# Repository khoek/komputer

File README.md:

# komputer

These are files (mainly programs) to help build a computer out of (relatively elementary) ICs.

There is a companion repository [khoek/kcpu-vm](https://github.com/khoek/kcpu-vm) which contains an assembler and hardware-simulating virtual machine for the architecture.

## Contents

- `circuits` - Designs for the various computer modules
- `embedded/tests` - Tests for the various modules
- `tools/eeagle` and `embedded/eeagle` - An EEPROM programmer client--server pair to talk to an Adafruit Metro Mini.

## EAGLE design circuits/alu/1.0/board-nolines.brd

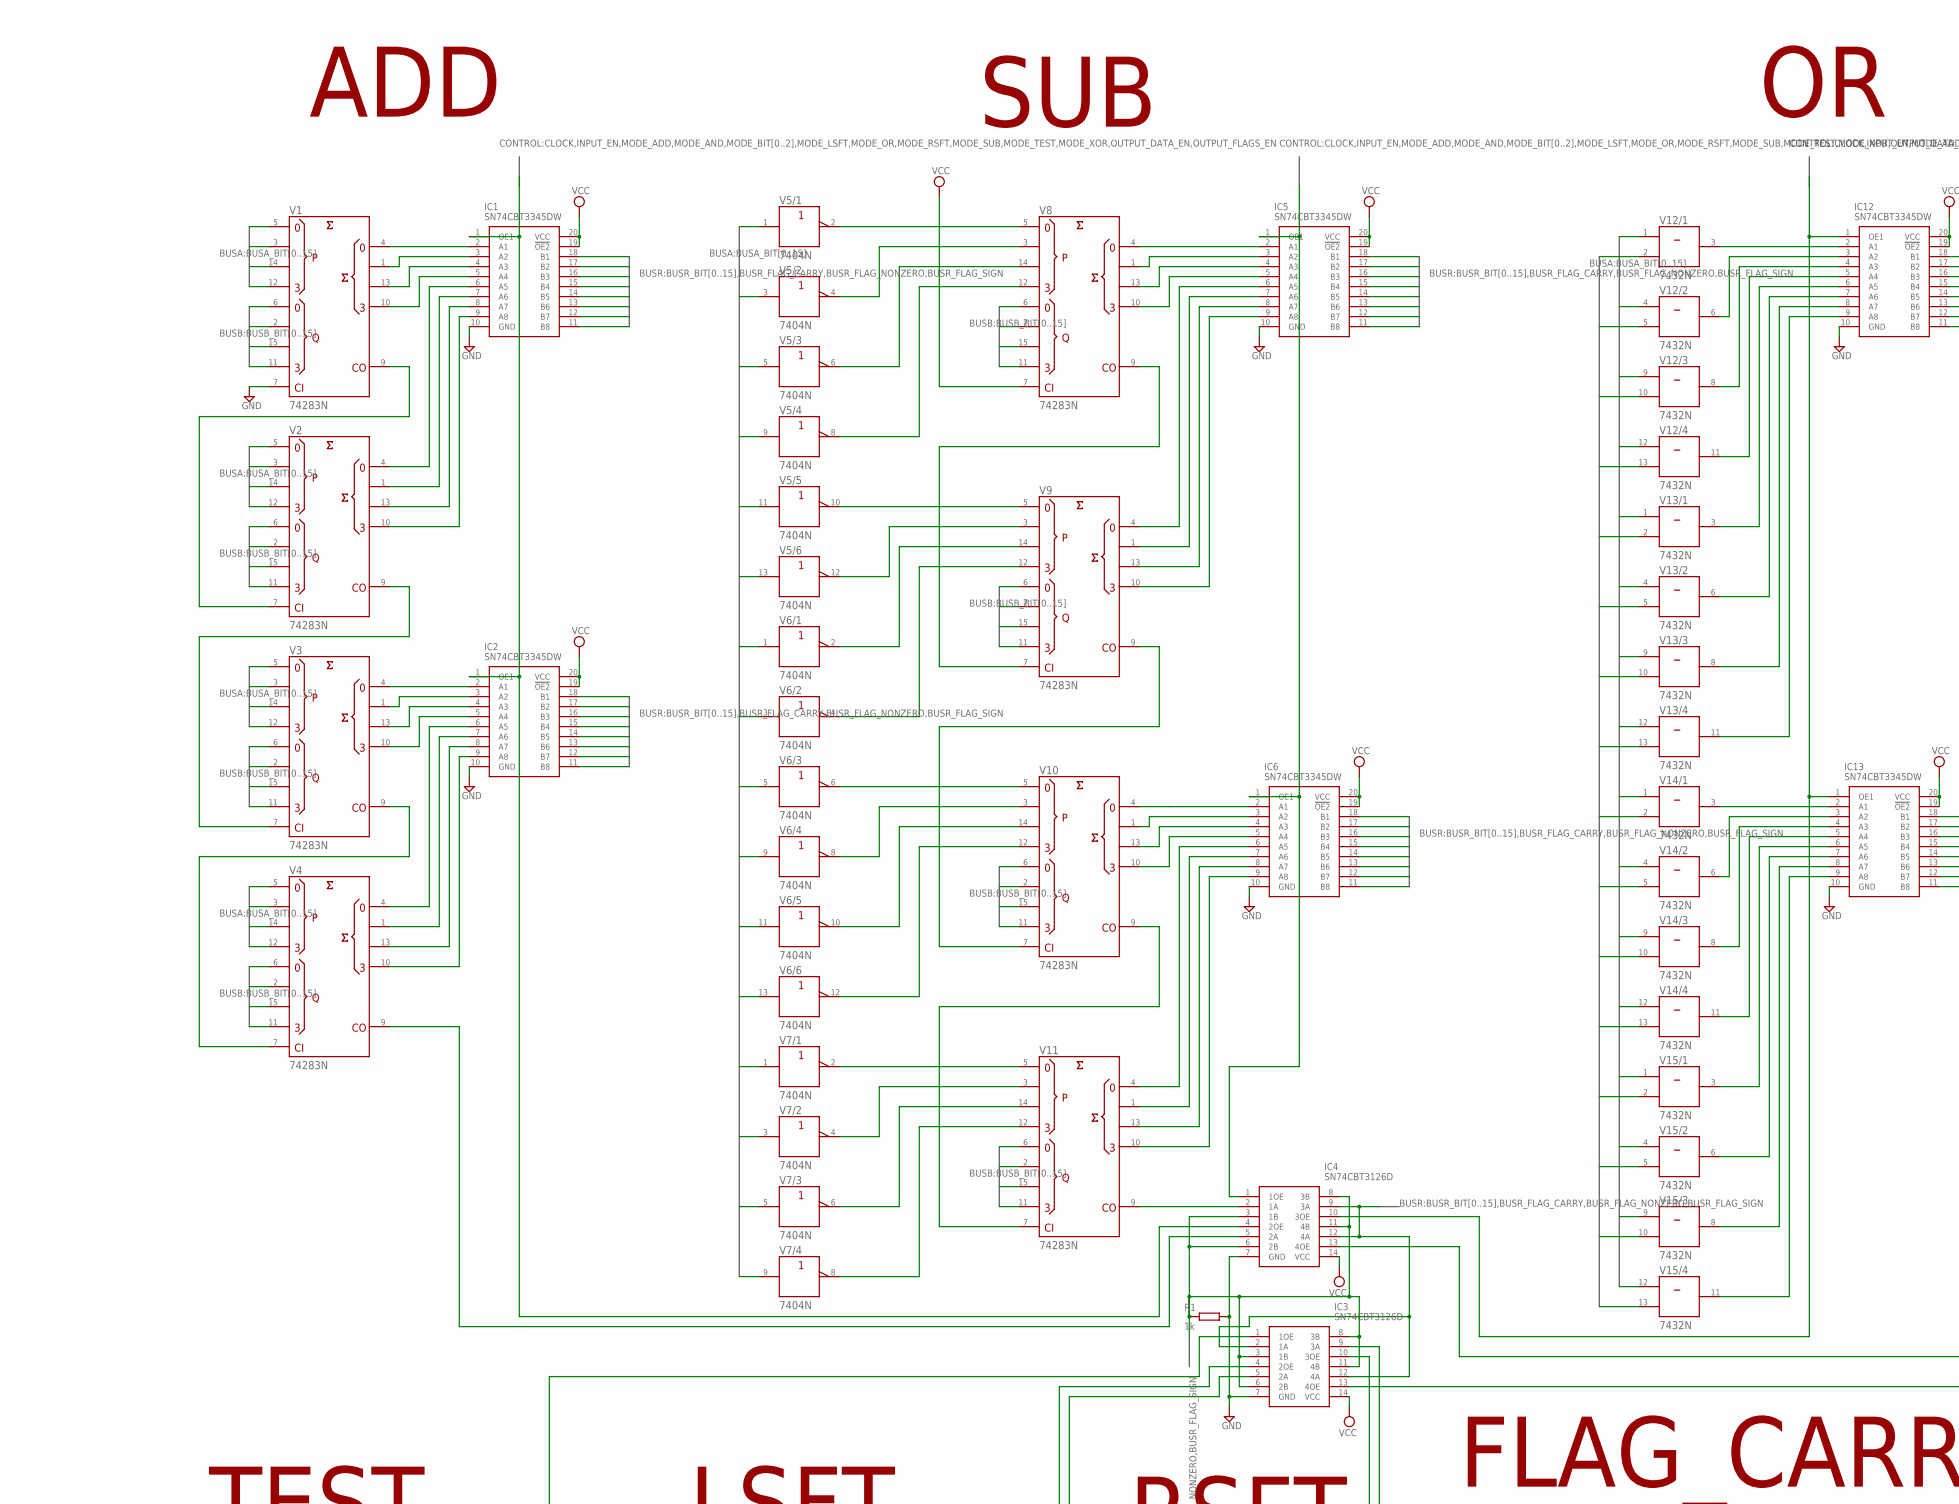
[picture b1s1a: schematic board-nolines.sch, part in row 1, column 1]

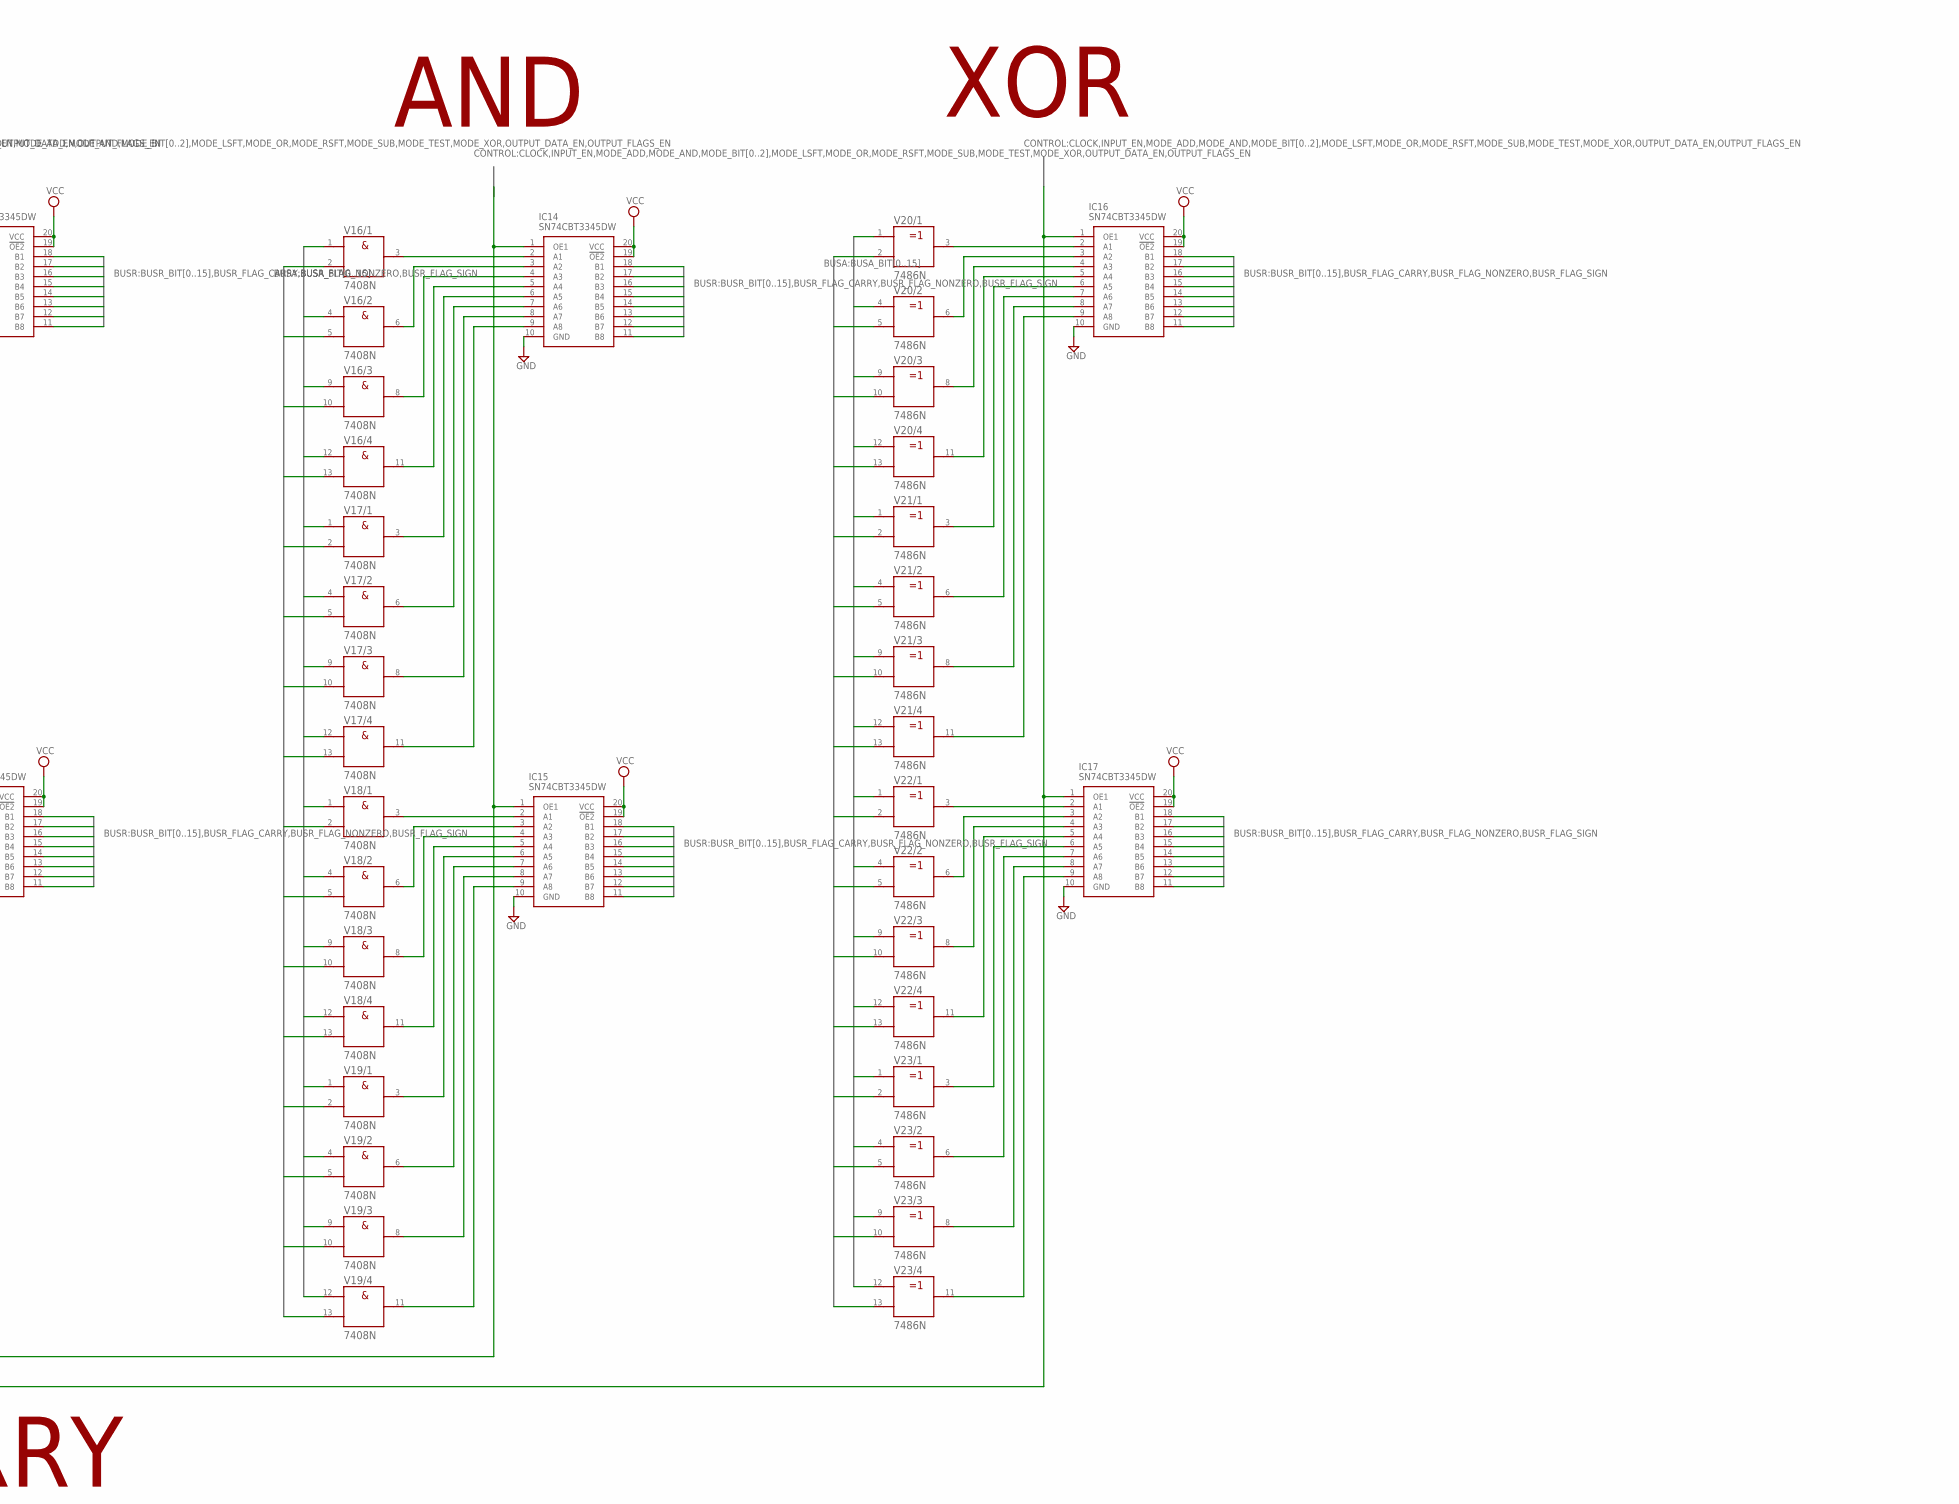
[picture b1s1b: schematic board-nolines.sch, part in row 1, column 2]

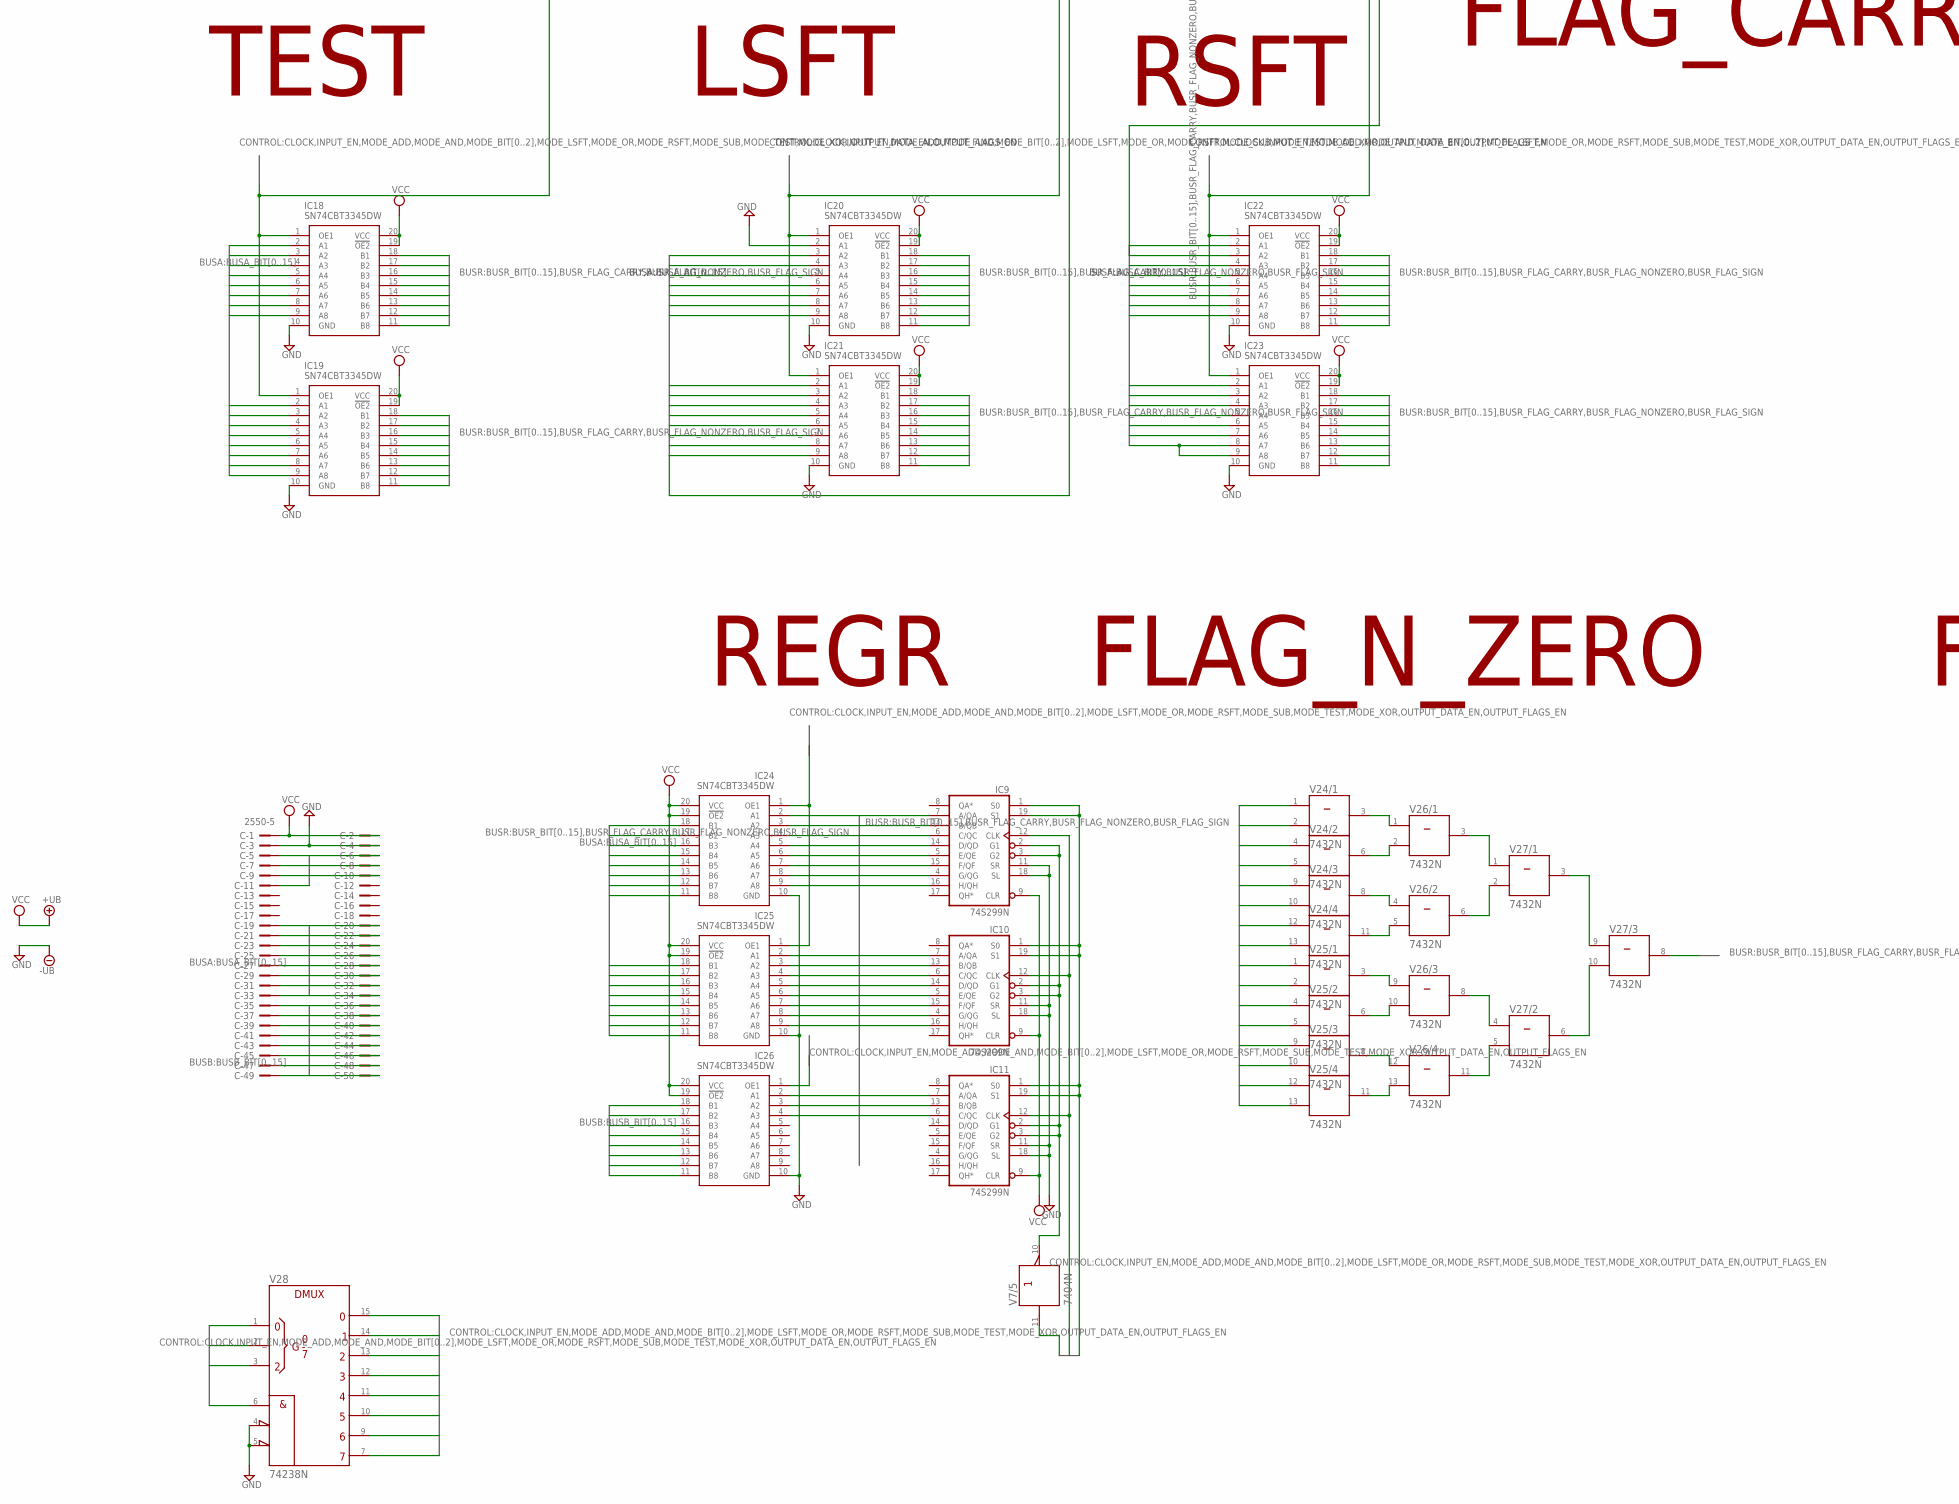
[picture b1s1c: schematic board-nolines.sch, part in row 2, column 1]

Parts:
C: 2550-5; PAK100/2500-5-50
IC1, IC2, IC5, IC6, IC12, IC13, IC14, IC15, IC16, IC17, IC18, IC19, IC20, IC21, IC22, IC23, IC24, IC25, IC26: SN74CBT3345DW; SOIC127P1030X265-20N
IC3, IC4: SN74CBT3126D; SOIC127P600X175-14N
IC9, IC10, IC11: 74S299N; DIL20
R1: 1k; 0207/10
V1, V2, V3, V4, V8, V9, V10, V11: 74283N; DIL16
V5, V6, V7: 7404N; DIL14
V12, V13, V14, V15, V24, V25, V26, V27: 7432N; DIL14
V16, V17, V18, V19: 7408N; DIL14
V20, V21, V22, V23: 7486N; DIL14
V28: 74238N; DIL16

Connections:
BUSA_BIT0: C.19, IC3.9 (3A), IC18.2 (A1), IC20.3 (A2), IC24.18 (B1), V1.5 (A1), V5.1 (A), V12.1 (A), V16.1 (A), V20.1 (A)
BUSA_BIT1: C.20, IC18.3 (A2), IC20.4 (A3), IC22.2 (A1), IC24.17 (B2), V1.3 (A2), V5.3 (A), V12.4 (A), V16.4 (A), V20.4 (A)
BUSA_BIT2: C.21, IC18.4 (A3), IC20.5 (A4), IC22.3 (A2), IC24.16 (B3), V1.14 (A3), V5.5 (A), V12.9 (A), V16.9 (A), V20.9 (A)
BUSA_BIT3: C.22, IC18.5 (A4), IC20.6 (A5), IC22.4 (A3), IC24.15 (B4), V1.12 (A4), V5.9 (A), V12.12 (A), V16.12 (A), V20.12 (A)
BUSA_BIT4: C.23, IC18.6 (A5), IC20.7 (A6), IC22.5 (A4), IC24.14 (B5), V2.5 (A1), V5.11 (A), V13.1 (A), V17.1 (A), V21.1 (A)
BUSA_BIT5: C.24, IC18.7 (A6), IC20.8 (A7), IC22.6 (A5), IC24.13 (B6), V2.3 (A2), V5.13 (A), V13.4 (A), V17.4 (A), V21.4 (A)
BUSA_BIT6: C.25, IC18.8 (A7), IC20.9 (A8), IC22.7 (A6), IC24.12 (B7), V2.14 (A3), V6.1 (A), V13.9 (A), V17.9 (A), V21.9 (A)
BUSA_BIT7: C.26, IC18.9 (A8), IC21.2 (A1), IC22.8 (A7), IC24.11 (B8), V2.12 (A4), V6.3 (A), V13.12 (A), V17.12 (A), V21.12 (A)
BUSA_BIT8: C.27, IC19.2 (A1), IC21.3 (A2), IC22.9 (A8), IC25.18 (B1), V3.5 (A1), V6.5 (A), V14.1 (A), V18.1 (A), V22.1 (A)
BUSA_BIT9: C.28, IC19.3 (A2), IC21.4 (A3), IC23.2 (A1), IC25.17 (B2), V3.3 (A2), V6.9 (A), V14.4 (A), V18.4 (A), V22.4 (A)
BUSA_BIT10: C.29, IC19.4 (A3), IC21.5 (A4), IC23.3 (A2), IC25.16 (B3), V3.14 (A3), V6.11 (A), V14.9 (A), V18.9 (A), V22.9 (A)
BUSA_BIT11: C.30, IC19.5 (A4), IC21.6 (A5), IC23.4 (A3), IC25.15 (B4), V3.12 (A4), V6.13 (A), V14.12 (A), V18.12 (A), V22.12 (A)
BUSA_BIT12: C.31, IC19.6 (A5), IC21.7 (A6), IC23.5 (A4), IC25.14 (B5), V4.5 (A1), V7.1 (A), V15.1 (A), V19.1 (A), V23.1 (A)
BUSA_BIT13: C.32, IC19.7 (A6), IC21.8 (A7), IC23.6 (A5), IC25.13 (B6), V4.3 (A2), V7.3 (A), V15.4 (A), V19.4 (A), V23.4 (A)
BUSA_BIT14: C.33, IC19.8 (A7), IC21.9 (A8), IC23.7 (A6), IC25.12 (B7), V4.14 (A3), V7.5 (A), V15.9 (A), V19.9 (A), V23.9 (A)
BUSA_BIT15: C.34, IC3.5 (2A), IC19.9 (A8), IC23.8 (A7), IC23.9 (A8), IC25.11 (B8), V4.12 (A4), V7.9 (A), V15.12 (A), V19.12 (A), V23.12 (A)
BUSB_BIT0: C.35, IC26.18 (B1), V1.6 (B1), V8.6 (B1), V12.2 (B), V16.2 (B), V20.2 (B)
BUSB_BIT1: C.36, IC26.17 (B2), V1.2 (B2), V8.2 (B2), V12.5 (B), V16.5 (B), V20.5 (B)
BUSB_BIT2: C.37, IC26.16 (B3), V1.15 (B3), V8.15 (B3), V12.10 (B), V16.10 (B), V20.10 (B)
BUSB_BIT3: C.38, IC26.15 (B4), V1.11 (B4), V8.11 (B4), V12.13 (B), V16.13 (B), V20.13 (B)
BUSB_BIT4: C.39, IC26.14 (B5), V2.6 (B1), V9.6 (B1), V13.2 (B), V17.2 (B), V21.2 (B)
BUSB_BIT5: C.40, IC26.13 (B6), V2.2 (B2), V9.2 (B2), V13.5 (B), V17.5 (B), V21.5 (B)
BUSB_BIT6: C.41, IC26.12 (B7), V2.15 (B3), V9.15 (B3), V13.10 (B), V17.10 (B), V21.10 (B)
BUSB_BIT7: C.42, IC26.11 (B8), V2.11 (B4), V9.11 (B4), V13.13 (B), V17.13 (B), V21.13 (B)
BUSB_BIT8: C.43, V3.6 (B1), V10.6 (B1), V14.2 (B), V18.2 (B), V22.2 (B)
BUSB_BIT9: C.44, V3.2 (B2), V10.2 (B2), V14.5 (B), V18.5 (B), V22.5 (B)
BUSB_BIT10: C.45, V3.15 (B3), V10.15 (B3), V14.10 (B), V18.10 (B), V22.10 (B)
BUSB_BIT11: C.46, V3.11 (B4), V10.11 (B4), V14.13 (B), V18.13 (B), V22.13 (B)
BUSB_BIT12: C.47, V4.6 (B1), V11.6 (B1), V15.2 (B), V19.2 (B), V23.2 (B)
BUSB_BIT13: C.48, V4.2 (B2), V11.2 (B2), V15.5 (B), V19.5 (B), V23.5 (B)
BUSB_BIT14: C.49, V4.15 (B3), V11.15 (B3), V15.10 (B), V19.10 (B), V23.10 (B)
BUSB_BIT15: C.50, V4.11 (B4), V11.11 (B4), V15.13 (B), V19.13 (B), V23.13 (B)
BUSR_BIT0: IC1.18 (B1), IC3.2 (1A), IC3.12 (4A), IC4.9 (3A), IC4.12 (4A), IC5.18 (B1), IC9.7 (A/QA), IC12.18 (B1), IC14.18 (B1), IC16.18 (B1), IC18.18 (B1), IC20.18 (B1), IC22.18 (B1), IC24.2 (A1), V24.1 (A)
BUSR_BIT1: IC1.17 (B2), IC5.17 (B2), IC9.13 (B/QB), IC12.17 (B2), IC14.17 (B2), IC16.17 (B2), IC18.17 (B2), IC20.17 (B2), IC22.17 (B2), IC24.3 (A2), V24.2 (B)
BUSR_BIT2: IC1.16 (B3), IC5.16 (B3), IC9.6 (C/QC), IC12.16 (B3), IC14.16 (B3), IC16.16 (B3), IC18.16 (B3), IC20.16 (B3), IC22.16 (B3), IC24.4 (A3), V24.4 (A)
BUSR_BIT3: IC1.15 (B4), IC5.15 (B4), IC9.14 (D/QD), IC12.15 (B4), IC14.15 (B4), IC16.15 (B4), IC18.15 (B4), IC20.15 (B4), IC22.15 (B4), IC24.5 (A4), V24.5 (B)
BUSR_BIT4: IC1.14 (B5), IC5.14 (B5), IC9.5 (E/QE), IC12.14 (B5), IC14.14 (B5), IC16.14 (B5), IC18.14 (B5), IC20.14 (B5), IC22.14 (B5), IC24.6 (A5), V24.9 (A)
BUSR_BIT5: IC1.13 (B6), IC5.13 (B6), IC9.15 (F/QF), IC12.13 (B6), IC14.13 (B6), IC16.13 (B6), IC18.13 (B6), IC20.13 (B6), IC22.13 (B6), IC24.7 (A6), V24.10 (B)
BUSR_BIT6: IC1.12 (B7), IC5.12 (B7), IC9.4 (G/QG), IC12.12 (B7), IC14.12 (B7), IC16.12 (B7), IC18.12 (B7), IC20.12 (B7), IC22.12 (B7), IC24.8 (A7), V24.12 (A)
BUSR_BIT7: IC1.11 (B8), IC5.11 (B8), IC9.16 (H/QH), IC12.11 (B8), IC14.11 (B8), IC16.11 (B8), IC18.11 (B8), IC20.11 (B8), IC22.11 (B8), IC24.9 (A8), V24.13 (B)
BUSR_BIT8: IC2.18 (B1), IC6.18 (B1), IC10.7 (A/QA), IC13.18 (B1), IC15.18 (B1), IC17.18 (B1), IC19.18 (B1), IC21.18 (B1), IC23.18 (B1), IC25.2 (A1), V25.1 (A)
BUSR_BIT9: IC2.17 (B2), IC6.17 (B2), IC10.13 (B/QB), IC13.17 (B2), IC15.17 (B2), IC17.17 (B2), IC19.17 (B2), IC21.17 (B2), IC23.17 (B2), IC25.3 (A2), V25.2 (B)
BUSR_BIT10: IC2.16 (B3), IC6.16 (B3), IC10.6 (C/QC), IC13.16 (B3), IC15.16 (B3), IC17.16 (B3), IC19.16 (B3), IC21.16 (B3), IC23.16 (B3), IC25.4 (A3), V25.4 (A)
BUSR_BIT11: IC2.15 (B4), IC6.15 (B4), IC10.14 (D/QD), IC13.15 (B4), IC15.15 (B4), IC17.15 (B4), IC19.15 (B4), IC21.15 (B4), IC23.15 (B4), IC25.5 (A4), V25.5 (B)
BUSR_BIT12: IC2.14 (B5), IC6.14 (B5), IC10.5 (E/QE), IC13.14 (B5), IC15.14 (B5), IC17.14 (B5), IC19.14 (B5), IC21.14 (B5), IC23.14 (B5), IC25.6 (A5), V25.9 (A)
BUSR_BIT13: IC2.13 (B6), IC6.13 (B6), IC10.15 (F/QF), IC13.13 (B6), IC15.13 (B6), IC17.13 (B6), IC19.13 (B6), IC21.13 (B6), IC23.13 (B6), IC25.7 (A6), V25.10 (B)
BUSR_BIT14: IC2.12 (B7), IC6.12 (B7), IC10.4 (G/QG), IC13.12 (B7), IC15.12 (B7), IC17.12 (B7), IC19.12 (B7), IC21.12 (B7), IC23.12 (B7), IC25.8 (A7), V25.12 (A)
BUSR_BIT15: IC2.11 (B8), IC6.11 (B8), IC10.16 (H/QH), IC13.11 (B8), IC15.11 (B8), IC17.11 (B8), IC19.11 (B8), IC21.11 (B8), IC23.11 (B8), IC25.9 (A8), V25.13 (B)
BUSR_FLAG_CARRY: IC3.3 (1B), IC3.6 (2B), IC3.8 (3B), IC3.11 (4B), IC4.3 (1B), IC4.6 (2B), IC4.8 (3B), IC4.11 (4B), IC11.7 (A/QA), IC26.2 (A1), R1.1
BUSR_FLAG_NONZERO: IC11.13 (B/QB), IC26.3 (A2), V27.8 (Y)
BUSR_FLAG_SIGN: IC11.6 (C/QC), IC26.4 (A3)
CLOCK: C.5, IC9.12 (CLK), IC10.12 (CLK), IC11.12 (CLK)
GND: C.3, C.4, IC1.10 (GND), IC2.10 (GND), IC3.7 (GND), IC4.7 (GND), IC5.10 (GND), IC6.10 (GND), IC9.10 (GND), IC9.11 (SR), IC9.18 (SL), IC10.10 (GND), IC10.11 (SR), IC10.18 (SL), IC11.10 (GND), IC11.11 (SR), IC11.18 (SL), IC12.10 (GND), IC13.10 (GND), IC14.10 (GND), IC15.10 (GND), IC16.10 (GND), IC17.10 (GND), IC18.10 (GND), IC19.10 (GND), IC20.2 (A1), IC20.10 (GND), IC21.10 (GND), IC22.10 (GND), IC23.10 (GND), IC24.10 (GND), IC25.10 (GND), IC26.10 (GND), R1.2, V1.7 (C0), V1.8 (-UB), V2.8 (-UB), V3.8 (-UB), V4.8 (-UB), V5.7 (-UB), V6.7 (-UB), V7.7 (-UB), V8.8 (-UB), V9.8 (-UB), V10.8 (-UB), V11.8 (-UB), V12.7 (-UB), V13.7 (-UB), V14.7 (-UB), V15.7 (-UB), V16.7 (-UB), V17.7 (-UB), V18.7 (-UB), V19.7 (-UB), V20.7 (-UB), V21.7 (-UB), V22.7 (-UB), V23.7 (-UB), V24.7 (-UB), V25.7 (-UB), V26.7 (-UB), V27.7 (-UB), V28.4 (!G2A), V28.5 (!G2B), V28.8 (-UB)
INPUT_EN: C.7, IC9.1 (S0), IC9.19 (S1), IC10.1 (S0), IC10.19 (S1), IC11.1 (S0), IC11.19 (S1), V28.6 (G1)
MODE_ADD: IC1.1 (OE1), IC2.1 (OE1), IC4.4 (2OE), V28.15 (Y0)
MODE_AND: IC4.13 (4OE), IC14.1 (OE1), IC15.1 (OE1), V28.13 (Y2)
MODE_BIT0: C.6, V28.1 (A)
MODE_BIT1: C.8, V28.2 (B)
MODE_BIT2: C.10, V28.3 (C)
MODE_LSFT: IC3.4 (2OE), IC20.1 (OE1), IC21.1 (OE1), V28.10 (Y5)
MODE_OR: IC4.10 (3OE), IC12.1 (OE1), IC13.1 (OE1), V28.12 (Y3)
MODE_RSFT: IC3.10 (3OE), IC22.1 (OE1), IC23.1 (OE1), V28.9 (Y6)
MODE_SUB: IC4.1 (1OE), IC5.1 (OE1), IC6.1 (OE1), V28.14 (Y1)
MODE_TEST: IC3.1 (1OE), IC18.1 (OE1), IC19.1 (OE1), V28.7 (Y7)
MODE_XOR: IC3.13 (4OE), IC16.1 (OE1), IC17.1 (OE1), V28.11 (Y4)
unnamed: V1.9 (C4), V2.7 (C0)
unnamed: V2.9 (C4), V3.7 (C0)
unnamed: V3.9 (C4), V4.7 (C0)
unnamed: V8.9 (C4), V9.7 (C0)
unnamed: V9.9 (C4), V10.7 (C0)
unnamed: V10.9 (C4), V11.7 (C0)
unnamed: V5.2 (Y), V8.5 (A1)
unnamed: V5.4 (Y), V8.3 (A2)
unnamed: V5.6 (Y), V8.14 (A3)
unnamed: V5.8 (Y), V8.12 (A4)
unnamed: V5.10 (Y), V9.5 (A1)
unnamed: V5.12 (Y), V9.3 (A2)
unnamed: V6.2 (Y), V9.14 (A3)
unnamed: V6.4 (Y), V9.12 (A4)
unnamed: V6.6 (Y), V10.5 (A1)
unnamed: V6.8 (Y), V10.3 (A2)
unnamed: V6.10 (Y), V10.14 (A3)
unnamed: V6.12 (Y), V10.12 (A4)
unnamed: V7.2 (Y), V11.5 (A1)
unnamed: V7.4 (Y), V11.3 (A2)
unnamed: V7.6 (Y), V11.14 (A3)
unnamed: V7.8 (Y), V11.12 (A4)
unnamed: IC1.2 (A1), V1.4 (S1)
unnamed: IC1.3 (A2), V1.1 (S2)
unnamed: IC1.4 (A3), V1.13 (S3)
unnamed: IC1.5 (A4), V1.10 (S4)
unnamed: IC1.6 (A5), V2.4 (S1)
unnamed: IC1.7 (A6), V2.1 (S2)
unnamed: IC1.8 (A7), V2.13 (S3)
unnamed: IC1.9 (A8), V2.10 (S4)
unnamed: IC2.2 (A1), V3.4 (S1)
unnamed: IC2.3 (A2), V3.1 (S2)
unnamed: IC2.4 (A3), V3.13 (S3)
unnamed: IC2.5 (A4), V3.10 (S4)
unnamed: IC2.6 (A5), V4.4 (S1)
unnamed: IC2.7 (A6), V4.1 (S2)
unnamed: IC2.8 (A7), V4.13 (S3)
unnamed: IC2.9 (A8), V4.10 (S4)
unnamed: IC5.2 (A1), V8.4 (S1)
unnamed: IC5.3 (A2), V8.1 (S2)
unnamed: IC5.4 (A3), V8.13 (S3)
unnamed: IC5.5 (A4), V8.10 (S4)
unnamed: IC5.6 (A5), V9.4 (S1)
unnamed: IC5.7 (A6), V9.1 (S2)
unnamed: IC5.8 (A7), V9.13 (S3)
unnamed: IC5.9 (A8), V9.10 (S4)
unnamed: IC6.2 (A1), V10.4 (S1)
unnamed: IC6.3 (A2), V10.1 (S2)
unnamed: IC4.5 (2A), V4.9 (C4)
unnamed: IC6.5 (A4), V10.10 (S4)
unnamed: IC6.6 (A5), V11.4 (S1)
unnamed: IC6.7 (A6), V11.1 (S2)
unnamed: IC6.8 (A7), V11.13 (S3)
unnamed: IC6.9 (A8), V11.10 (S4)
unnamed: IC13.8 (A7), V15.8 (Y)
unnamed: IC6.4 (A3), V10.13 (S3)
unnamed: IC4.2 (1A), V11.9 (C4)
unnamed: IC14.2 (A1), V16.3 (Y)
unnamed: V24.3 (Y), V26.1 (A)
unnamed: IC14.3 (A2), V16.6 (Y)
unnamed: IC12.2 (A1), V12.3 (Y)
unnamed: IC9.2 (G1), IC9.3 (G2), IC10.2 (G1), IC10.3 (G2), IC11.2 (G1), IC11.3 (G2), V7.10 (Y)
unnamed: IC12.3 (A2), V12.6 (Y)
unnamed: IC14.5 (A4), V16.11 (Y)
unnamed: IC12.5 (A4), V12.11 (Y)
unnamed: IC12.6 (A5), V13.3 (Y)
unnamed: IC12.7 (A6), V13.6 (Y)
unnamed: IC14.6 (A5), V17.3 (Y)
unnamed: IC12.9 (A8), V13.11 (Y)
unnamed: IC13.2 (A1), V14.3 (Y)
unnamed: IC14.7 (A6), V17.6 (Y)
unnamed: IC13.4 (A3), V14.8 (Y)
unnamed: IC13.5 (A4), V14.11 (Y)
unnamed: IC13.6 (A5), V15.3 (Y)
unnamed: IC14.9 (A8), V17.11 (Y)
unnamed: IC15.2 (A1), V18.3 (Y)
unnamed: IC15.4 (A3), V18.8 (Y)
unnamed: IC15.5 (A4), V18.11 (Y)
unnamed: IC15.6 (A5), V19.3 (Y)
unnamed: IC12.4 (A3), V12.8 (Y)
unnamed: IC14.4 (A3), V16.8 (Y)
unnamed: IC14.8 (A7), V17.8 (Y)
unnamed: IC15.3 (A2), V18.6 (Y)
unnamed: IC12.8 (A7), V13.8 (Y)
unnamed: IC15.7 (A6), V19.6 (Y)
unnamed: IC15.9 (A8), V19.11 (Y)
unnamed: IC13.3 (A2), V14.6 (Y)
unnamed: IC15.8 (A7), V19.8 (Y)
unnamed: IC16.2 (A1), V20.3 (Y)
unnamed: IC13.7 (A6), V15.6 (Y)
unnamed: IC16.3 (A2), V20.6 (Y)
unnamed: IC13.9 (A8), V15.11 (Y)
unnamed: IC16.5 (A4), V20.11 (Y)
unnamed: IC16.6 (A5), V21.3 (Y)
unnamed: IC16.7 (A6), V21.6 (Y)
unnamed: IC16.9 (A8), V21.11 (Y)
unnamed: IC17.2 (A1), V22.3 (Y)
unnamed: IC17.4 (A3), V22.8 (Y)
unnamed: IC17.5 (A4), V22.11 (Y)
unnamed: IC17.6 (A5), V23.3 (Y)
unnamed: IC16.4 (A3), V20.8 (Y)
unnamed: IC16.8 (A7), V21.8 (Y)
unnamed: IC17.3 (A2), V22.6 (Y)
unnamed: IC17.7 (A6), V23.6 (Y)
unnamed: IC17.9 (A8), V23.11 (Y)
unnamed: IC17.8 (A7), V23.8 (Y)
unnamed: V24.6 (Y), V26.2 (B)
unnamed: V24.11 (Y), V26.5 (B)
unnamed: V25.6 (Y), V26.10 (B)
unnamed: V25.11 (Y), V26.13 (B)
unnamed: V26.11 (Y), V27.5 (B)
unnamed: V26.6 (Y), V27.2 (B)
unnamed: V26.3 (Y), V27.1 (A)
unnamed: V26.8 (Y), V27.4 (A)
unnamed: V27.6 (Y), V27.10 (B)
unnamed: V27.3 (Y), V27.9 (A)
unnamed: V25.3 (Y), V26.9 (A)
unnamed: V24.8 (Y), V26.4 (A)
unnamed: V25.8 (Y), V26.12 (A)
OUTPUT_DATA_EN: C.9, IC24.1 (OE1), IC25.1 (OE1), V7.11 (A)
OUTPUT_FLAGS_EN: C.11, IC26.1 (OE1)
VCC: C.1, C.2, IC1.19 (!OE2), IC1.20 (VCC), IC2.19 (!OE2), IC2.20 (VCC), IC3.14 (VCC), IC4.14 (VCC), IC5.19 (!OE2), IC5.20 (VCC), IC6.19 (!OE2), IC6.20 (VCC), IC9.9 (CLR), IC9.20 (VCC), IC10.9 (CLR), IC10.20 (VCC), IC11.9 (CLR), IC11.20 (VCC), IC12.19 (!OE2), IC12.20 (VCC), IC13.19 (!OE2), IC13.20 (VCC), IC14.19 (!OE2), IC14.20 (VCC), IC15.19 (!OE2), IC15.20 (VCC), IC16.19 (!OE2), IC16.20 (VCC), IC17.19 (!OE2), IC17.20 (VCC), IC18.19 (!OE2), IC18.20 (VCC), IC19.19 (!OE2), IC19.20 (VCC), IC20.19 (!OE2), IC20.20 (VCC), IC21.19 (!OE2), IC21.20 (VCC), IC22.19 (!OE2), IC22.20 (VCC), IC23.19 (!OE2), IC23.20 (VCC), IC24.19 (!OE2), IC24.20 (VCC), IC25.19 (!OE2), IC25.20 (VCC), IC26.19 (!OE2), IC26.20 (VCC), V1.16 (+UB), V2.16 (+UB), V3.16 (+UB), V4.16 (+UB), V5.14 (+UB), V6.14 (+UB), V7.14 (+UB), V8.7 (C0), V8.16 (+UB), V9.16 (+UB), V10.16 (+UB), V11.16 (+UB), V12.14 (+UB), V13.14 (+UB), V14.14 (+UB), V15.14 (+UB), V16.14 (+UB), V17.14 (+UB), V18.14 (+UB), V19.14 (+UB), V20.14 (+UB), V21.14 (+UB), V22.14 (+UB), V23.14 (+UB), V24.14 (+UB), V25.14 (+UB), V26.14 (+UB), V27.14 (+UB), V28.16 (+UB)

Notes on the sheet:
ADD
SUB
AND
XOR
TEST
LSFT
RSFT
REGR
FLAG_N_ZERO
FLAG_CARRY
FLAG_SIGN

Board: 2 copper layers, 54 parts (11 on the bottom side), 187 nets, no tracks yet.

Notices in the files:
parts and their libraries:
microbuilder: This work is placed in the public domain, and may be freely used for commercial and non-commercial work with the following conditions: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
